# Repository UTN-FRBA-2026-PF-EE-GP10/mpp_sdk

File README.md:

<div align="center">

# mpp-sdk

</div>

A Python SDK for designing, comparing, and deploying **Maximum Power Point
Tracking** (MPPT) algorithms for photovoltaic systems. Built around a clean
hardware-abstraction seam so the same controller code drives a simulation
today and a real SEPIC converter on a Host/sbc tomorrow.

See [`AGENTS.md`](./AGENTS.md) for architectural pillars and contribution
guidelines. Open work is tracked in the
[project tracker issue](https://github.com/UTN-FRBA-2026-PF-EE-GP10/mpp_sdk/issues/128).

## Why

The Python PV ecosystem has a strong **modelling** library
([`pvlib-python`](https://pvlib-python.readthedocs.io/)) but no shared
**control** library. pvlib gives you the panel physics. It does not give
you the closed-loop algorithms that decide where on the I-V curve to
operate. Most MPPT comparison work in the literature uses MATLAB/Simulink,
with code that is rarely released and per-paper bespoke metrics. That
makes cross-paper comparisons and sim-to-real validation hard to
reproduce [Subudhi & Pradhan 2013].

`mpp-sdk` closes that gap with four contributions:

1. **A uniform `MPPTAlgorithm.step(V, I) → D` interface.** A new
   controller is a one-file PR, and the comparison harness treats it like
   every other algorithm.
2. **A hardware-abstraction seam (`SignalSource`).** The same algorithm
   code runs against a `SimulatedSource` or a real power-electronics
   board, with no branches in the algorithm.
3. **A microcontroller as the deployment target.** A small MCU
   (Raspberry Pi Pico / RP2040) drives the power stage, connected to the
   Host/sbc over SPI. This isolates the fast-switching, high-current
   side from the Host/sbc, and gives the project its deployment target: once an
   algorithm is validated in the framework, it is ported to the MCU and
   re-run end to end on the same physical rig.
4. **A reproducible comparison harness.** Dynamic irradiance profiles,
   shared metrics (tracking efficiency, settling time, steady-state
   oscillation, trap depth), and paper figures regenerated from code.

> **The thesis deliverable is an MCU-deployable algorithm that fits a
> Pico-class chip and performs competitively with classical methods.**
> The same codebase both develops it and compares it against the
> established literature. The MCU-deployment requirement is also a useful
> design constraint: it favors fixed-step, minimal-state methods, which
> also happen to be the easiest to analyse.

The design reasoning and the related-work background live in
[`docs/rationale.md`](docs/rationale.md) and
[`docs/general_information.md`](docs/general_information.md).

## Installation

Once published to PyPI, install with `uv` (recommended) or `pip`:

```bash
# Core library - panel models, SEPIC converter, P&O, SimulatedSource
uv add mpp-sdk

# With high-fidelity pvlib panel models (PvlibPanelModel adapter)
uv add "mpp-sdk[pvlib]"

# With SPI hardware dependencies (Phase 5 - SpiMcuSource)
uv add "mpp-sdk[hardware]"

# With the curve-tracer FastAPI web backend (mpp-sdk curve-tracer-web)
uv add "mpp-sdk[web]"

# Everything at once
uv add "mpp-sdk[all]"
```

Then import from your project:

```python
import mpp_sdk

panel = mpp_sdk.IdealSingleDiode()
conv  = mpp_sdk.SEPICConverter()
src   = mpp_sdk.SimulatedSource(panel, conv, load_resistance=10.0)
ctl   = mpp_sdk.PerturbAndObserve(initial_duty=src.duty, min_duty=0.1, max_duty=0.9)

for _ in range(500):
    v, i = src.read()
    src.write(ctl.step(v, i))
```

## Quickstart (development)

Clone the repo and run the live demo directly:

```bash
git clone https://github.com/UTN-FRBA-2026-PF-EE-GP10/mpp_sdk.git
cd mpp_sdk
uv sync
uv run main.py
```

This runs Perturb & Observe MPPT against the ideal single-diode panel model
and plots the I-V / P-V curves with the calculated MPP and the algorithm's
operating-point trajectory.

Every other runnable script under `harness/`, `examples/`, and `scripts/`
is also reachable through one dispatcher, `mpp-sdk`
(`examples/pno_demo.py` is a thin shim to this same `main.py` quickstart,
so it is not a separate entry):

```bash
uv run mpp-sdk --help              # list every runnable script
uv run mpp-sdk compare-dynamic     # run harness/compare_dynamic.py
uv run mpp-sdk animate --shade     # forwards extra flags to the target script
```

Each script also stays directly runnable on its own (e.g.
`uv run harness/compare_dynamic.py`) - `mpp-sdk` is just a single place to
discover them all.

### Curve-tracer web workbench

A React frontend + FastAPI backend for capturing, browsing, and replaying
real panel I-V curves - see [`frontend/README.md`](frontend/README.md) for
the full picture. Try it with no hardware at all:

```bash
uv sync --extra web
uv run mpp-sdk curve-tracer-web --demo
# open http://localhost:8000/
```

Drop `--demo` (and add `--extra hardware`) once a Raspberry Pi + RP2040
board is wired up per
[`firmware/pipico_board/README.md`](firmware/pipico_board/README.md).

### Closed-loop runs

`mpp-sdk run-algorithm --algorithm "P&O" --duration-s 10 --label bench-check`
sweeps a ground-truth I-V curve, then runs a registered algorithm against
the live board for a while, recording `(t, V, I, D)`. Plot it with
`mpp-sdk plot-run`. Needs real hardware (`--extra hardware`).

## Layout

```text
mpp_sdk/
├── models/         # Solar panel I-V models  (PanelModel ABC; ideal, pvlib, string, tabulated, measured)
├── converters/     # Power-stage models      (SEPICConverter)
├── algorithms/     # MPPT controllers        (MPPTAlgorithm ABC; P&O, InCond, fuzzy, scan, PSO)
├── io/             # Hardware-abstraction    (SignalSource ABC; simulated, dynamic, noisy, SPI to the Pico)
├── curves/         # Captured I-V curve library (CurveRecord, feeds MeasuredPanel)
├── runs/           # Captured closed-loop runs (RunRecord)
├── sessions/       # Bench session checklists and their templates
├── panels/         # Panel model library (label values)
├── metrics.py      # Comparison metrics
└── visualization.py

harness/            # Comparison scripts (static, dynamic, live, cyclic ranking, sim-to-real bank)
scripts/            # Bench tools and the workbench server (FastAPI)
frontend/           # Workbench UI (React); its build is committed to scripts/curve_tracer_web/
firmware/           # RP2040 firmware (Rust) and its host-tested safety-checks crate
hardware/           # KiCad board
data/               # Bench data (see data/README.md)
docs/               # Algorithm references, rationale, procedures
```

The control variable is always the SEPIC **duty cycle**. The measured
quantities are always panel terminal **voltage** and **current**. Richer
panel models may depend on temperature, irradiance, or a measured curve,
but those inputs live on the *model* - the controller never sees them.

## Where mpp-sdk sits relative to pvlib

[`pvlib-python`](https://pvlib-python.readthedocs.io/) is the de-facto
open-source reference for photovoltaic system *performance modelling* in
Python: solar position, irradiance decomposition and transposition,
single- and two-diode I-V solvers, the `bishop88` reverse-bias method for
partial-shading analysis, temperature models, and inverter/energy-yield
calculations [Anderson et al. 2023].

**pvlib does not provide closed-loop MPPT controllers, time-stepping
controller simulation, or hardware abstraction.** Its analytical
`bishop88_mpp` and single-diode MPP solvers return *the* maximum power
point given panel parameters. They do not implement Perturb & Observe,
Incremental Conductance, fuzzy logic, or any other tracking algorithm
that discovers the MPP from a stream of (V, I) measurements.

`mpp-sdk` fills that gap. It is **complementary** to pvlib, not a
replacement:

| Concern                                  | pvlib            | mpp-sdk            |
| ---------------------------------------- | ---------------- | ------------------ |
| Solar resource & irradiance models       | yes              | out of scope       |
| Panel I-V physics (single / two-diode)   | yes (canonical)  | minimal in-tree    |
| Partial shading via `bishop88`           | yes              | wraps pvlib        |
| Closed-loop MPPT controllers (P&O, …)    | **no**           | **yes**            |
| SEPIC / power-stage model                | no               | yes                |
| Hardware abstraction (`SignalSource`)    | no               | yes (Pi + Pico)    |
| Algorithm benchmark / comparison harness | no               | yes                |

The `PvlibPanelModel(PanelModel)` adapter (shipped) drops any pvlib-grade
model behind our controller and converter pipeline, unchanged. We do not
re-implement panel physics that pvlib already provides.

## Status

- **Shipped:** panel models (ideal, pvlib, string, measured), five
  algorithms, the comparison harness, the curve tracer, the web
  workbench, and the Pi + Pico firmware.
- **On hardware:** curves are good. Closed-loop runs work for P&O. The
  other algorithms need a slower, settled control loop first.
- **Open:** a valid hardware comparison, the algorithm port to the Pico,
  and the thesis figures.

Open work is tracked in the [project tracker issue](https://github.com/UTN-FRBA-2026-PF-EE-GP10/mpp_sdk/issues/128).

## Context

This SDK supports an **Electronics Engineering thesis** on MPPT algorithm
comparison. One hard rule applies: **each part of the SDK must work and be
verified in isolation** before it is integrated (see
[`AGENTS.md`](./AGENTS.md), "Definition of done").

The MIT license (see [`LICENSE`](./LICENSE)) covers redistribution. It is
not a warranty: whoever wires this code to real hardware is responsible
for electrical safety and for checking the code against their own
measurements.

## On the use of AI

This project uses large language models (Claude, ChatGPT, Copilot) as
part of its day-to-day toolchain. That is a deliberate choice, not
something to apologise for.

The thesis has **no external funding**. The team is three people with
limited weekly hours. Comparable research groups routinely have either
dedicated funding or AI-assisted workflows, or both. Refusing to use AI
would not buy us purity - it would just widen the resource gap between
this work and the groups it is benchmarked against. We use AI for the
same reason we use `pvlib` instead of re-implementing single-diode
physics: the leverage is real, and the alternative is to do less
science.

That choice has explicit guardrails:

- **Disclose.** The thesis names the LLMs used and the tasks they helped
  with.
- **Verify.** A person reads, understands, and tests every LLM-assisted
  change before it merges.
- **Cite.** When an LLM reproduces a known algorithm or formula, the
  change cites the primary reference.
- **Author.** A person is the author of every commit and is accountable
  for it.
- **Off-limits.** Numerical results, measured data, experimental claims,
  and conclusions are written and checked by the human authors.

## References

The bibliography below is the working set the project cites; it will grow
as algorithms and models land.

### Reference Python framework

- **[Anderson et al. 2023]** Anderson, K. S., Hansen, C. W., Holmgren,
  W. F., Jensen, A. R., Mikofski, M. A., & Driesse, A. (2023). *pvlib
  python: 2023 project update.* Journal of Open Source Software,
  **8**(92), 5994. <https://doi.org/10.21105/joss.05994>
- **[Holmgren et al. 2018]** Holmgren, W. F., Hansen, C. W., & Mikofski,
  M. A. (2018). *pvlib python: a python package for modeling solar
  energy systems.* Journal of Open Source Software, **3**(29), 884.
  <https://doi.org/10.21105/joss.00884>

### Panel modelling

- **[De Soto et al. 2006]** De Soto, W., Klein, S. A., & Beckman, W. A.
  (2006). *Improvement and validation of a model for photovoltaic array
  performance.* Solar Energy, **80**(1), 78-88. (Single-diode model
  parameter extraction.)

### MPPT algorithm reviews and canonical methods

- **[Andriniriniaimalaza et al. 2025]** Andriniriniaimalaza, F. P., Murad,
  N. M., Balan, G., Bilal, H., Randriatefison, N., Khoodaruth, A.,
  Andrianirina, C. B., & Ravelo, B. (2025). *Hybrid Fuzzy Logic and
  Shading-Aware Particle Swarm Optimization for Dynamic Photovoltaic
  Shading Faults Mitigation.* arXiv. <https://doi.org/10.48550/arXiv.2512.08419>
- **[Subudhi & Pradhan 2013]** Subudhi, B., & Pradhan, R. (2013). *A
  comparative study on maximum power point tracking techniques for
  photovoltaic power systems.* IEEE Transactions on Sustainable Energy,
  **4**(1), 89-98.
- **[Hussein et al. 1995]** Hussein, K. H., Muta, I., Hoshino, T., &
  Osakada, M. (1995). *Maximum photovoltaic power tracking: an
  algorithm for rapidly changing atmospheric conditions.* IEE
  Proceedings - Generation, Transmission and Distribution, **142**(1),
  59-64. (Incremental Conductance reference implementation.)
- **[Femia et al. 2005]** Femia, N., Petrone, G., Spagnuolo, G., &
  Vitelli, M. (2005). *Optimization of perturb and observe maximum
  power point tracking method.* IEEE Transactions on Power Electronics,
  **20**(4), 963-973. (P&O step-size design.)
- **[Kobayashi et al. 2006]** Kobayashi, K., Takano, I., & Sawada, Y.
  (2006). *A study of a two stage maximum power point tracking control of
  a photovoltaic system under partially shaded insolation conditions.*
  Solar Energy Materials and Solar Cells, **90**(18), 2975-2988.

### Partial shading and Global MPPT

- **[Patel & Agarwal 2008]** Patel, H., & Agarwal, V. (2008). *Maximum
  power point tracking scheme for PV systems operating under partially
  shaded conditions.* IEEE Transactions on Industrial Electronics,
  **55**(4), 1689-1698.
- **[Miyatake et al. 2011]** Miyatake, M., Veerachary, M., Toriumi, F.,
  Fujii, N., & Ko, H. (2011). *Maximum power point tracking of multiple
  photovoltaic arrays: a PSO approach.* IEEE Transactions on Aerospace
  and Electronic Systems, **47**(1), 367-380.
- **[Liu et al. 2012]** Liu, Y.-H., Huang, S.-C., Huang, J.-W., & Liang,
  W.-C. (2012). *A particle swarm optimization-based maximum power
  point tracking algorithm for PV systems operating under partially
  shaded conditions.* IEEE Transactions on Energy Conversion, **27**(4),
  1027-1035.

### Standards and benchmarking

- **[EN 50530]** CENELEC EN 50530:2010+A1:2013. *Overall efficiency of
  grid connected photovoltaic inverters.* (Defines the MPPT
  static- and dynamic-efficiency test profiles used as the comparison
  harness target.)

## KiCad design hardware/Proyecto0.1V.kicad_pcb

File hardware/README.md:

# Hardware

KiCad source for the Proyecto 0.1V board, plus generated fabrication/export
artifacts. Source and generated files live side by side in this folder -
here's which is which.

## Source (edit these)

- `Proyecto0.1V.kicad_pro`, `Proyecto0.1V.kicad_pcb` - the KiCad project and
  PCB layout.
- `Proyecto0.1V.kicad_sch`, `Pico.kicad_sch`, `SepicConverter.kicad_sch`,
  `supplies.kicad_sch` - hierarchical schematic sheets.
- `untitled.kicad_sch` - despite the name, this **is** live source: the
  AnalogConverters sensing sheet. It's badly named, not stray - don't
  delete or rename it (renaming a sheet file requires a KiCad project-level
  edit for zero functional gain).
- `Custom_Library.pretty/` - custom footprint library used by the layout.

## Generated (regenerate, don't hand-edit)

- `Proyecto0.1V-schematic.pdf`, `Proyecto0.1V-pcb.pdf` - schematic/PCB PDF
  exports, generated with kicad-cli 10.0.1:

  ```sh
  kicad-cli sch export pdf Proyecto0.1V.kicad_sch \
      -o Proyecto0.1V-schematic.pdf
  kicad-cli pcb export pdf Proyecto0.1V.kicad_pcb \
      -o Proyecto0.1V-pcb.pdf \
      -l F.Cu,B.Cu,F.SilkS,B.SilkS,F.Fab,B.Fab,Edge.Cuts \
      --cl Edge.Cuts --mode-multipage --include-border-title
  ```

- `jlcpcb/gerber/`, `jlcpcb/production_files/` - JLCPCB fabrication outputs
  (Gerbers, drill files, BOM, CPL) generated from the KiCad project's own
  fabrication-output tooling.

Regenerate the PDFs and JLCPCB outputs after any schematic/layout change -
don't let them drift from the source files.

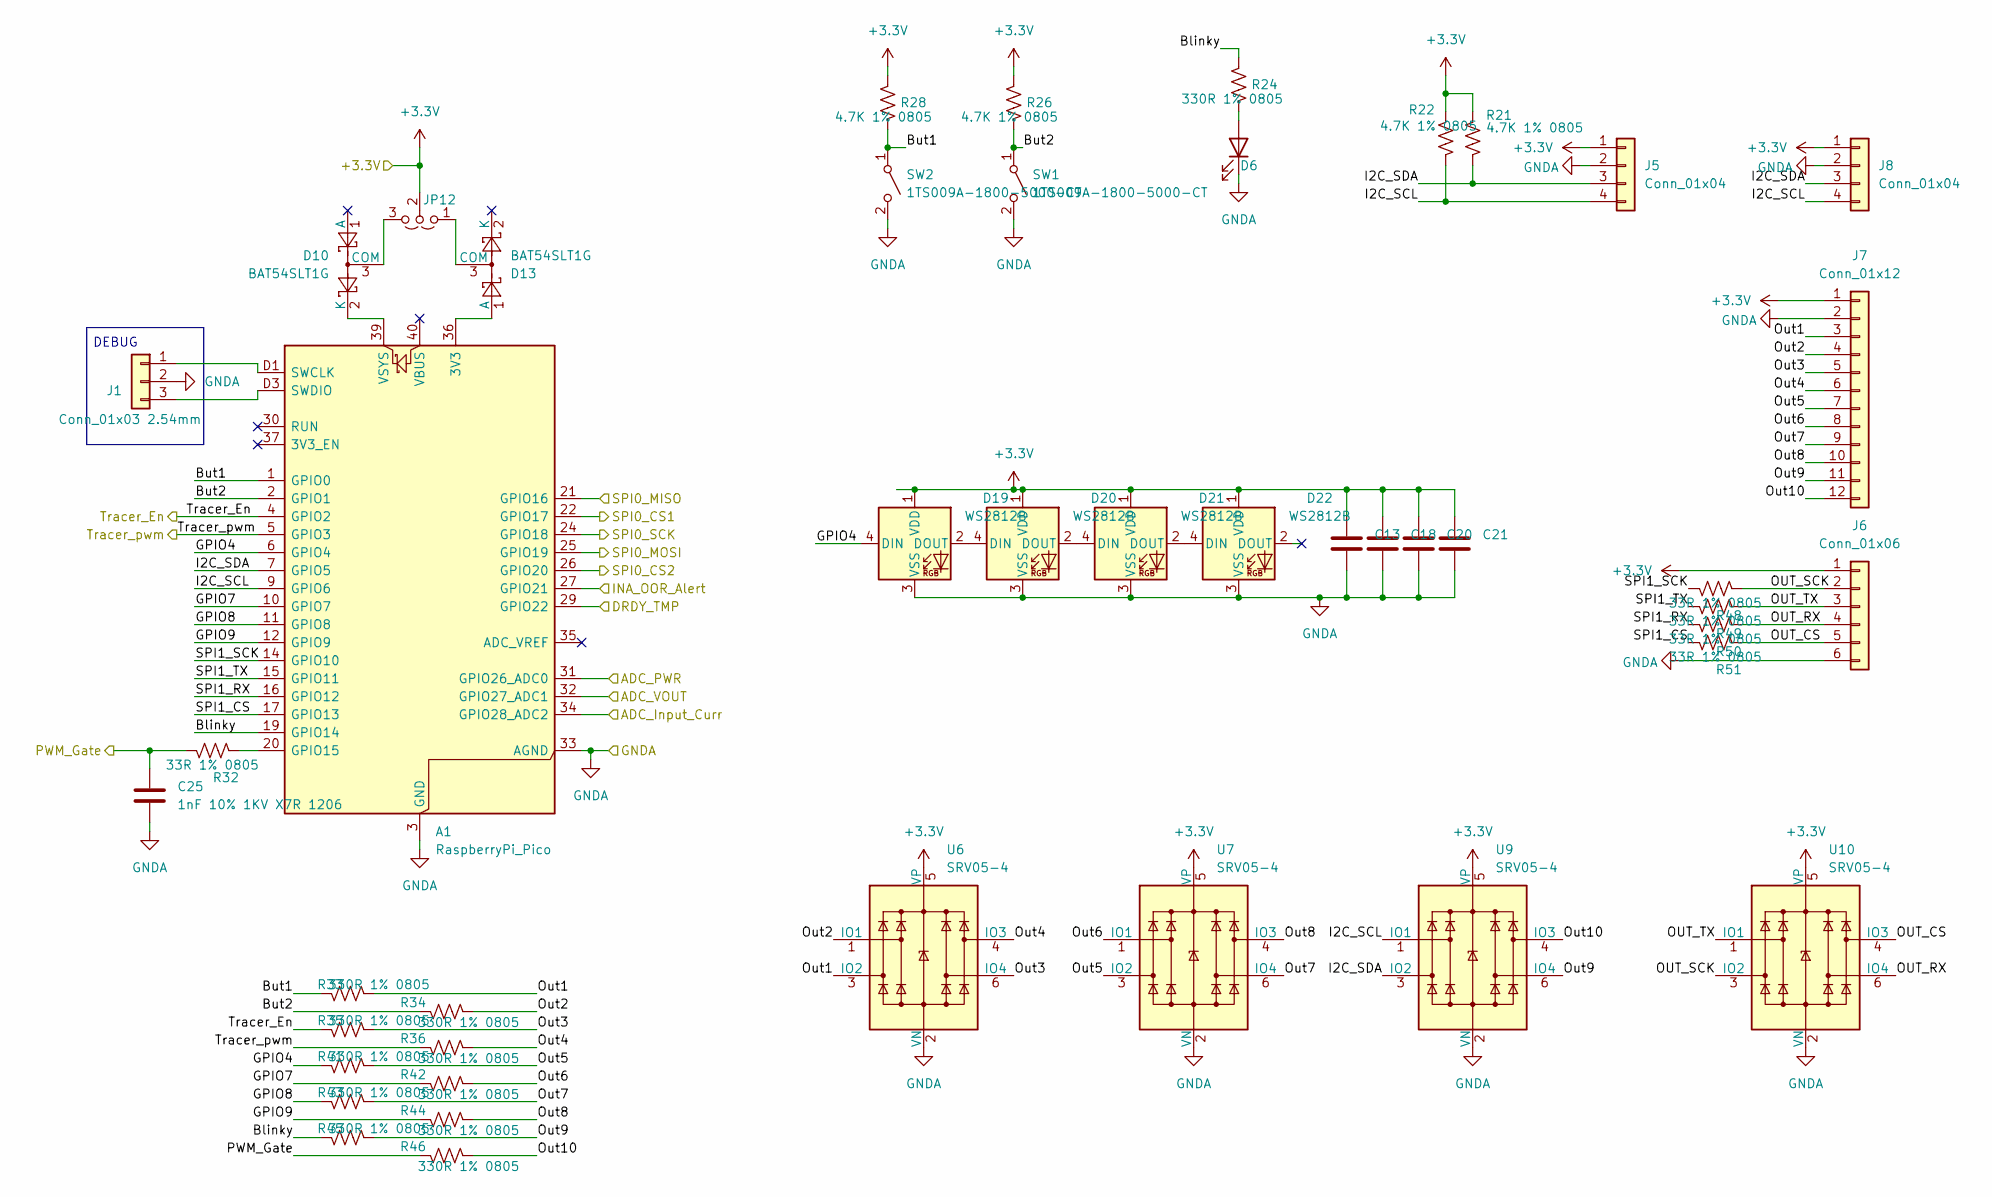
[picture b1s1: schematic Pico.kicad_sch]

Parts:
A1: RaspberryPi_Pico; RaspberryPi_Pico_SMD_HandSolder
C13, C18, C20, C21: 100nF 10% 50V X7R 0805; C_0805_2012Metric
C25: 1nF 10% 1KV X7R 1206; C_1206_3216Metric
D6: YLED0805 Red; LED_0805_2012Metric
D10, D13: BAT54SLT1G; SOT-23; LCSC Part C19726
D19, D20, D21, D22: WS2812B; LED_WS2812B_PLCC4_5.0x5.0mm_P3.2mm
J1: Conn_01x03 2.54mm; PinHeader_1x03_P2.54mm_Vertical
J5, J8: Conn_01x04; PinHeader_1x04_P2.54mm_Vertical
J6: Conn_01x06; PinHeader_1x06_P2.54mm_Vertical
J7: Conn_01x12; PinHeader_1x12_P2.54mm_Vertical
JP12: 2/3 Wire Selector; PinHeader_1x03_P2.54mm_Vertical
R21, R22, R26, R28: 4.7K 1% 0805; R_0805_2012Metric
R24, R33, R34, R35, R36, R41, R42, R43, R44, R45, R46: 330R 1% 0805; R_0805_2012Metric
R32, R48, R49, R50, R51: 33R 1% 0805; R_0805_2012Metric
SW1, SW2: 1TS009A-1800-5000-CT; SW_Push_1TS009xxxx-xxxx-xxxx_6x6x5mm; LCSC Part C319409
U6, U7, U9, U10: SRV05-4; SOT-23-6; LCSC Part C1975211

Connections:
+3.3V: C13.1, C18.1, C20.1, C21.1, D19.1 (VDD), D20.1 (VDD), D21.1 (VDD), D22.1 (VDD), J5.1, J6.1, J7.1, J8.1, JP12.2 (C), R21.2, R22.2, R26.1, R28.1, U6.5 (VP), U7.5 (VP), U9.5 (VP), U10.5 (VP); also elsewhere on the board
/AnalogConverters/ADC_Input_Curr: A1.34 (GPIO28_ADC2); also elsewhere on the board
/AnalogConverters/ADC_VOUT: A1.32 (GPIO27_ADC1); also elsewhere on the board
/AnalogConverters/ADC_VPWR: A1.31 (GPIO26_ADC0); also elsewhere on the board
/AnalogConverters/CS_INA: A1.22 (GPIO17); also elsewhere on the board
/AnalogConverters/CS_TP100: A1.26 (GPIO20); also elsewhere on the board
/AnalogConverters/DRDY_PT100: A1.29 (GPIO22); also elsewhere on the board
/AnalogConverters/INA_OOR_Alert: A1.27 (GPIO21); also elsewhere on the board
/AnalogConverters/SPI_MISO: A1.21 (GPIO16); also elsewhere on the board
/AnalogConverters/SPI_MOSI: A1.25 (GPIO19); also elsewhere on the board
/AnalogConverters/SPI_SCK: A1.24 (GPIO18); also elsewhere on the board
/Pico/Blinky: A1.19 (GPIO14), R24.1, R45.1
/Pico/But1: A1.1 (GPIO0), R28.2, R33.1, SW2.1 (A)
/Pico/But2: A1.2 (GPIO1), R26.2, R34.1, SW1.1 (A)
/Pico/GPIO4: A1.6 (GPIO4), D19.4 (DIN), R41.1
/Pico/GPIO7: A1.10 (GPIO7), R42.1
/Pico/GPIO8: A1.11 (GPIO8), R43.1
/Pico/GPIO9: A1.12 (GPIO9), R44.1
/Pico/I2C_SCL: A1.9 (GPIO6), J5.4, J8.4, R22.1, U9.1 (IO1)
/Pico/I2C_SDA: A1.7 (GPIO5), J5.3, J8.3, R21.1, U9.3 (IO2)
/Pico/OUT_CS: J6.5, R51.2, U10.4 (IO3)
/Pico/OUT_RX: J6.4, R50.2, U10.6 (IO4)
/Pico/OUT_SCK: J6.2, R48.2, U10.3 (IO2)
/Pico/OUT_TX: J6.3, R49.2, U10.1 (IO1)
/Pico/Out1: J7.3, R33.2, U6.3 (IO2)
/Pico/Out2: J7.4, R34.2, U6.1 (IO1)
/Pico/Out3: J7.5, R35.2, U6.6 (IO4)
/Pico/Out4: J7.6, R36.2, U6.4 (IO3)
/Pico/Out5: J7.7, R41.2, U7.3 (IO2)
/Pico/Out6: J7.8, R42.2, U7.1 (IO1)
/Pico/Out7: J7.9, R43.2, U7.6 (IO4)
/Pico/Out8: J7.10, R44.2, U7.4 (IO3)
/Pico/Out9: J7.11, R45.2, U9.6 (IO4)
/Pico/Out10: J7.12, R46.2, U9.4 (IO3)
/Pico/PWM_Gate: C25.1, R32.1, R46.1; also elsewhere on the board
/Pico/SPI1_CS: A1.17 (GPIO13), R51.1
/Pico/SPI1_RX: A1.16 (GPIO12), R50.1
/Pico/SPI1_SCK: A1.14 (GPIO10), R48.1
/Pico/SPI1_TX: A1.15 (GPIO11), R49.1
/Pico/Tracer_En: A1.4 (GPIO2), R35.1; also elsewhere on the board
/Pico/Tracer_pwm: A1.5 (GPIO3), R36.1; also elsewhere on the board
GNDA: A1.3 (GND), A1.8 (GND), A1.13 (GND), A1.18 (GND), A1.23 (GND), A1.28 (GND), A1.33 (AGND), A1.38 (GND), A1.D2 (GND), C13.2, C18.2, C20.2, C21.2, C25.2, D6.1 (K), D19.3 (VSS), D20.3 (VSS), D21.3 (VSS), D22.3 (VSS), J1.2, J5.2, J6.6, J7.2, J8.2, SW1.2 (B), SW2.2 (B), U6.2 (VN), U7.2 (VN), U9.2 (VN), U10.2 (VN); also elsewhere on the board
unnamed: A1.36 (3V3), D13.1 (A)
unnamed: A1.20 (GPIO15), R32.2
unnamed: A1.D1 (SWCLK), J1.1
unnamed: A1.D3 (SWDIO), J1.3
unnamed: A1.39 (VSYS), D10.2 (K)
unnamed: D6.2 (A), R24.2
unnamed: D10.3 (COM), JP12.3 (B)
unnamed: D13.3 (COM), JP12.1 (A)
unnamed: D19.2 (DOUT), D20.4 (DIN)
unnamed: D20.2 (DOUT), D21.4 (DIN)
unnamed: D21.2 (DOUT), D22.4 (DIN)

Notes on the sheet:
DEBUG

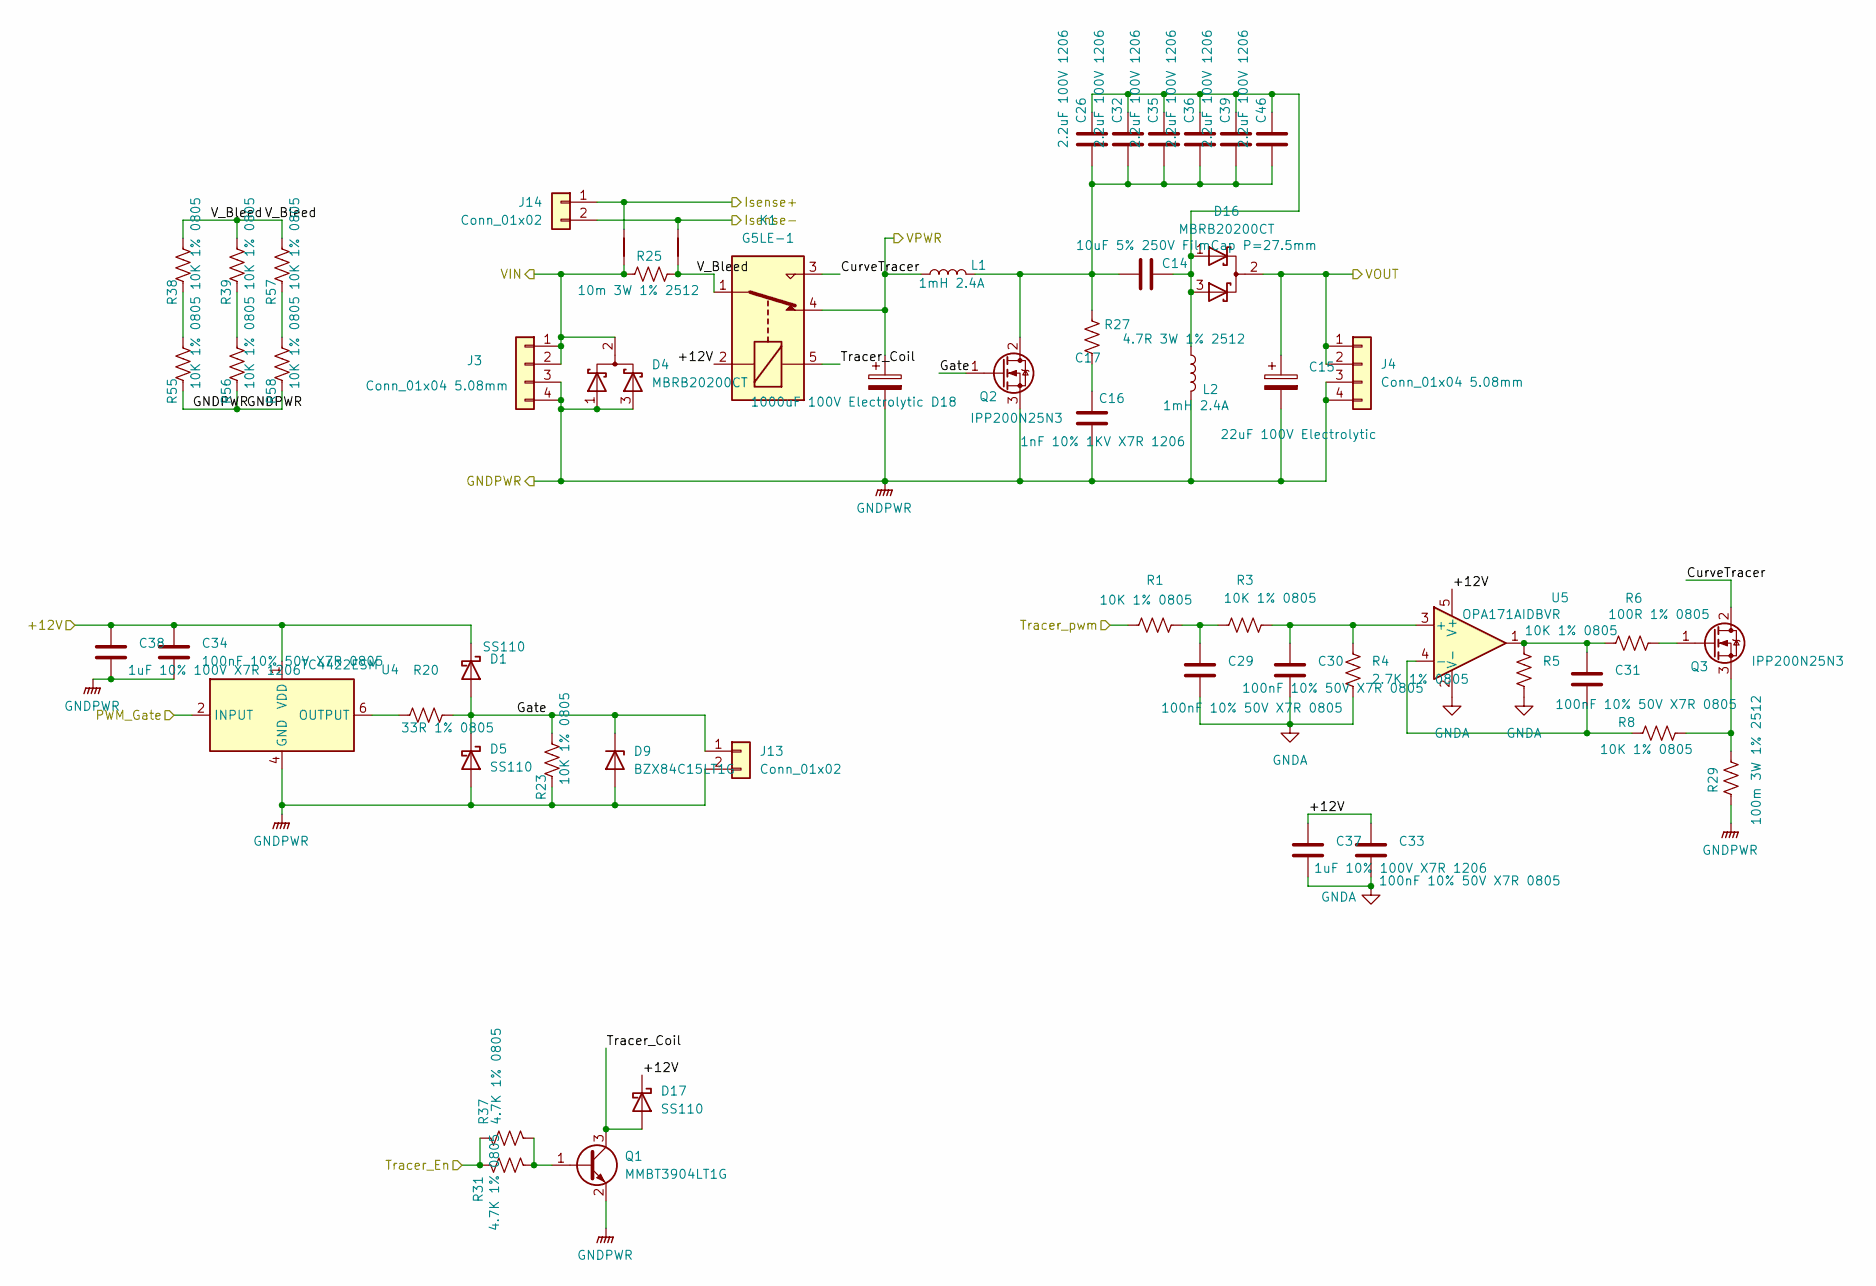
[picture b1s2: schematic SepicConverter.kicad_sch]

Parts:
C14: 10uF 5% 250V FilmCap P=27.5mm; C_Rect_L31.5mm_W17.0mm_P27.50mm_MKS4
C15: 22uF 100V Electrolytic; CP_Radial_D6.3mm_P2.50mm
C16: 1nF 10% 1KV X7R 1206; C_1206_3216Metric
C17: 1000uF 100V Electrolytic D18; CP_Radial_D18.0mm_P7.50mm
C26, C32, C35, C36, C39, C46: 2.2uF 100V 1206; C_1206_3216Metric
C29, C30, C31, C33, C34: 100nF 10% 50V X7R 0805; C_0805_2012Metric
C37, C38: 1uF 10% 100V X7R 1206; C_1206_3216Metric
D1, D5, D17: SS110; D_SMA_Handsoldering
D4, D16: MBRB20200CT; TO-263-2; LCSC Part C3874012
D9: BZX84C15LT1G; SOT-23; LCSC Part C80857
J3, J4: Conn_01x04 5.08mm; TerminalBlock_Phoenix_MKDS-1,5-4-5.08_1x04_P5.08mm_Horizont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
J13, J14: Conn_01x02; PinHeader_1x02_P2.54mm_Vertical
K1: G5LE-1; Relay_SPDT_Omron-G5LE-1
L1, L2: 1mH 2.4A; L_Toroid_Vertical_L31.8mm_W15.9mm_P13.50mm_Bourns_5700
NT1, NT2: NetTie_2; NetTie-2_SMD_Pad0.5mm
Q1: MMBT3904LT1G; SOT-23; LCSC Part C81464
Q2, Q3: IPP200N25N3; TO-220-3_Vertical
R1, R3, R5, R8, R23, R38, R39, R55, R56, R57, R58: 10K 1% 0805; R_0805_2012Metric
R4: 2.7K 1% 0805; R_0805_2012Metric
R6: 100R 1% 0805; R_0805_2012Metric
R20: 33R 1% 0805; R_0805_2012Metric
R25: 10m 3W 1% 2512; R_2512_6332Metric
R27: 4.7R 3W 1% 2512; R_2512_6332Metric
R29: 100m 3W 1% 2512; R_2512_6332Metric
R31, R37: 4.7K 1% 0805; R_0805_2012Metric
U4: TC4422ESM; SOIC-8_5.3x5.3mm_P1.27mm; LCSC Part C638566
U5: OPA171AIDBVR; SOT-23-5; LCSC Part C88036

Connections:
+12V: C33.1, C34.1, C37.1, C38.1, D1.1 (K), D17.1 (K), K1.2, U4.1 (VDD), U4.8 (VDD), U5.5 (V+); also elsewhere on the board
/AnalogConverters/Isense+: J14.1, NT1.2; also elsewhere on the board
/AnalogConverters/Isense-: J14.2, NT2.2; also elsewhere on the board
/AnalogConverters/VIN: D4.2 (K), J3.1, J3.2, NT1.1, R25.1; also elsewhere on the board
/AnalogConverters/VOUT: C15.1, D16.2 (K), J4.1, J4.2; also elsewhere on the board
/AnalogConverters/VPWR: C17.1, K1.4, L1.1; also elsewhere on the board
/Pico/PWM_Gate: U4.2 (INPUT); also elsewhere on the board
/Pico/Tracer_En: R31.2, R37.2; also elsewhere on the board
/Pico/Tracer_pwm: R1.1; also elsewhere on the board
/SepicConverter/CurveTracer: K1.3, Q3.2 (D)
/SepicConverter/Gate: D1.2 (A), D5.1 (K), D9.3 (K), J13.1, Q2.1 (G), R20.2, R23.2
/SepicConverter/Tracer_Coil: D17.2 (A), K1.5, Q1.3 (C)
/SepicConverter/V_Bleed: K1.1, NT2.1, R25.2, R38.2, R39.2, R57.2
GNDA: C29.2, C30.2, C33.2, C37.2, R4.1, R5.1, U5.2 (V-); also elsewhere on the board
GNDPWR: C15.2, C16.1, C17.2, C34.2, C38.2, D4.1 (A), D4.3 (A), D5.2 (A), D9.1 (A), J3.3, J3.4, J4.3, J4.4, J13.2, L2.2, Q1.2 (E), Q2.3 (S), R23.1, R29.1, R55.1, R56.1, R58.1, U4.4 (GND), U4.5 (GND); also elsewhere on the board
unnamed: C14.2, C26.2, C32.2, C35.2, C36.2, C39.2, C46.2, D16.1 (A), D16.3 (A), L2.1
unnamed: C16.2, R27.1
unnamed: C29.1, R1.2, R3.1
unnamed: C31.1, R5.2, R6.2, U5.1
unnamed: Q1.1 (B), R31.1, R37.1
unnamed: C14.1, C26.1, C32.1, C35.1, C36.1, C39.1, C46.1, L1.2, Q2.2 (D), R27.2
unnamed: Q3.1 (G), R6.1
unnamed: Q3.3 (S), R8.1, R29.2
unnamed: R20.1, U4.6 (OUTPUT), U4.7 (OUTPUT)
unnamed: R38.1, R55.2
unnamed: R39.1, R56.2
unnamed: R57.1, R58.2
unnamed: C30.1, R3.2, R4.2, U5.3 (+)
unnamed: C31.2, R8.2, U5.4 (-)

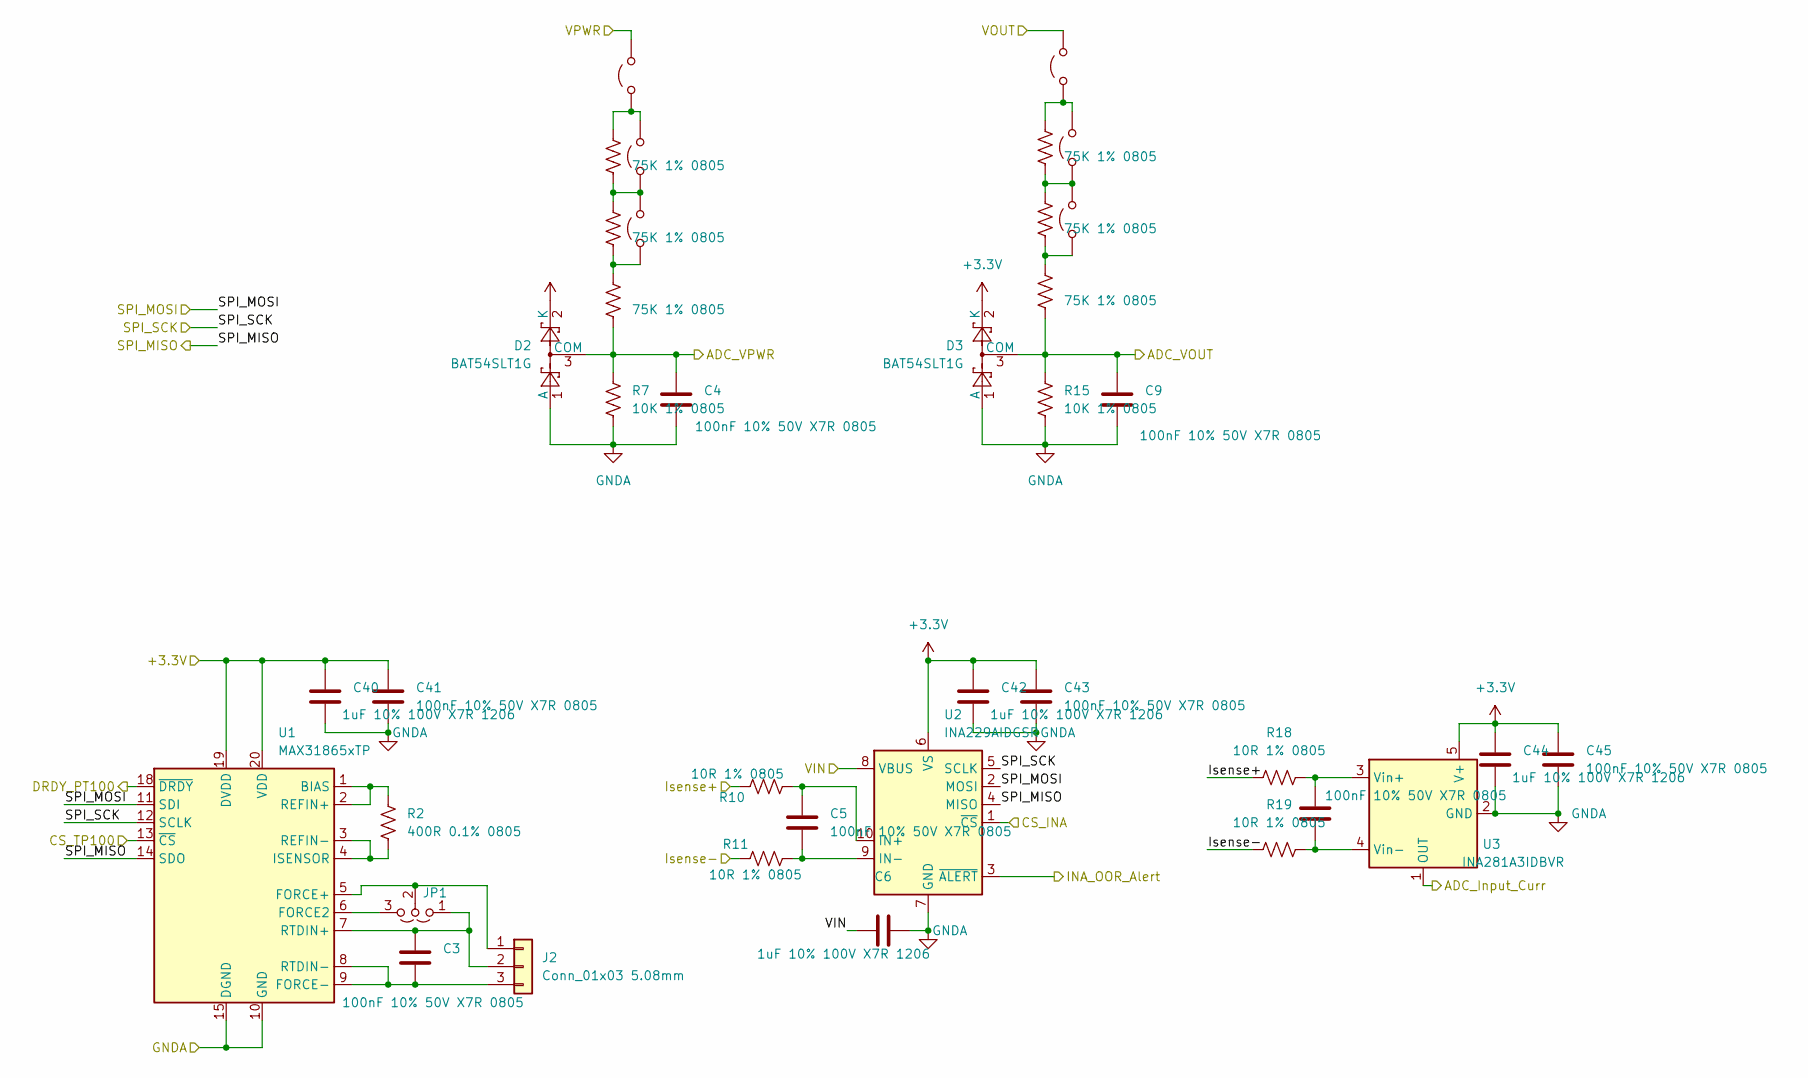
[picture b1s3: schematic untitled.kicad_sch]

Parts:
C3, C4, C5, C9, C10, C41, C43, C45: 100nF 10% 50V X7R 0805; C_0805_2012Metric
C6, C40, C42, C44: 1uF 10% 100V X7R 1206; C_1206_3216Metric
D2, D3: BAT54SLT1G; SOT-23; LCSC Part C19726
J2: Conn_01x03 5.08mm; TerminalBlock_Phoenix_MKDS-1,5-3-5.08_1x03_P5.08mm_Horizont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
JP1: 2/3 Wire Selector; PinHeader_1x03_P2.54mm_Vertical
JP6, JP7, JP8, JP9, JP10, JP13: Jumper_2_Open; PinHeader_1x02_P2.54mm_Vertical
R2: 400R 0.1% 0805; R_0805_2012Metric
R7, R15: 10K 1% 0805; R_0805_2012Metric
R10, R11, R18, R19: 10R 1% 0805; R_0805_2012Metric
R12, R13, R14, R16, R17, R30: 75K 1% 0805; R_0805_2012Metric
U1: MAX31865xTP; TQFN-20-1EP_5x5mm_P0.65mm_EP3.25x3.25mm; LCSC Part C118474
U2: INA229AIDGSR; TSSOP-10_3x3mm_P0.5mm; LCSC Part C2846803
U3: INA281A3IDBVR; SOT-23-5; LCSC Part C1517407

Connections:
+3.3V: C40.1, C41.1, C42.1, C43.1, C44.1, C45.1, D2.2 (K), D3.2 (K), U1.19 (DVDD), U1.20 (VDD), U2.6 (VS), U3.5 (V+); also elsewhere on the board
/AnalogConverters/ADC_Input_Curr: U3.1 (OUT); also elsewhere on the board
/AnalogConverters/ADC_VOUT: C9.1, D3.3 (COM), R15.1, R30.2; also elsewhere on the board
/AnalogConverters/ADC_VPWR: C4.1, D2.3 (COM), R7.1, R14.2; also elsewhere on the board
/AnalogConverters/CS_INA: U2.1 (~CS); also elsewhere on the board
/AnalogConverters/CS_TP100: U1.13 (~CS); also elsewhere on the board
/AnalogConverters/DRDY_PT100: U1.18 (~DRDY); also elsewhere on the board
/AnalogConverters/INA_OOR_Alert: U2.3 (~ALERT); also elsewhere on the board
/AnalogConverters/Isense+: R10.1, R18.1; also elsewhere on the board
/AnalogConverters/Isense-: R11.1, R19.1; also elsewhere on the board
/AnalogConverters/SPI_MISO: U1.14 (SDO), U2.4 (MISO); also elsewhere on the board
/AnalogConverters/SPI_MOSI: U1.11 (SDI), U2.2 (MOSI); also elsewhere on the board
/AnalogConverters/SPI_SCK: U1.12 (SCLK), U2.5 (SCLK); also elsewhere on the board
/AnalogConverters/VIN: C6.1, U2.8 (VBUS); also elsewhere on the board
/AnalogConverters/VOUT: JP10.2 (B); also elsewhere on the board
/AnalogConverters/VPWR: JP9.2 (B); also elsewhere on the board
GNDA: C4.2, C6.2, C9.2, C40.2, C41.2, C42.2, C43.2, C44.2, C45.2, D2.1 (A), D3.1 (A), R7.2, R15.2, U1.10 (GND), U1.15 (DGND), U1.16 (GND), U1.21 (GND), U2.7 (GND), U3.2 (GND); also elsewhere on the board
unnamed: J2.1, JP1.2 (C), U1.5 (FORCE+)
unnamed: C3.1, J2.2, JP1.1 (A), U1.7 (RTDIN+)
unnamed: C3.2, J2.3, U1.8 (RTDIN-), U1.9 (FORCE-)
unnamed: JP1.3 (B), U1.6 (FORCE2)
unnamed: JP6.1 (A), JP7.2 (B), R12.1, R13.2
unnamed: JP6.2 (B), JP9.1 (A), R13.1
unnamed: JP7.1 (A), R12.2, R14.1
unnamed: JP8.2 (B), JP10.1 (A), R16.1
unnamed: JP13.1 (A), R17.2, R30.1
unnamed: JP8.1 (A), JP13.2 (B), R16.2, R17.1
unnamed: R2.2, U1.1 (BIAS), U1.2 (REFIN+)
unnamed: R2.1, U1.3 (REFIN-), U1.4 (ISENSOR)
unnamed: C5.1, R10.2, U2.10 (IN+)
unnamed: C5.2, R11.2, U2.9 (IN-)
unnamed: C10.1, R18.2, U3.3 (Vin+)
unnamed: C10.2, R19.2, U3.4 (Vin-)

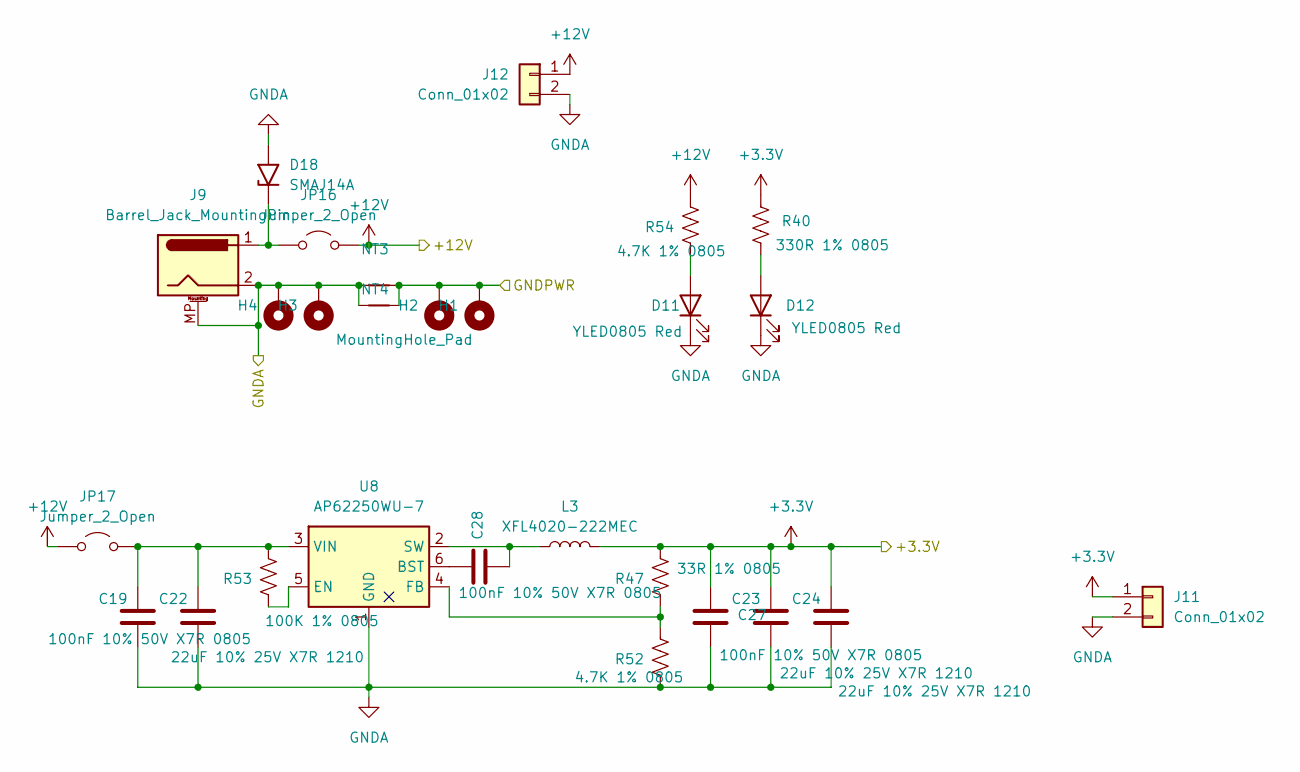
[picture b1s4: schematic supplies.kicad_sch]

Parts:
C19, C27, C28: 100nF 10% 50V X7R 0805; C_0805_2012Metric
C22, C23, C24: 22uF 10% 25V X7R 1210; C_1210_3225Metric
D11, D12: YLED0805 Red; LED_0805_2012Metric
D18: SMAJ14A; D_SMA; LCSC Part C99286
H1, H2, H3, H4: MountingHole_Pad; MountingHole_3.2mm_M3_Pad
J9: Barrel_Jack_MountingPin; BarrelJack_GCT_DCJ200-10-A_Horizontal
J11, J12: Conn_01x02; PinHeader_1x02_P2.54mm_Vertical
JP16, JP17: Jumper_2_Open; PinHeader_1x02_P2.54mm_Vertical
L3: XFL4020-222MEC; L_Wurth_WE-LQSH-4020; LCSC Part C122469
NT3, NT4: NetTie_2; NetTie-2_SMD_Pad2.0mm
R40: 330R 1% 0805; R_0805_2012Metric
R47: 33R 1% 0805; R_0805_2012Metric
R52, R54: 4.7K 1% 0805; R_0805_2012Metric
R53: 100K 1% 0805; R_0805_2012Metric
U8: AP62250WU-7; TSOT-23-6; LCSC Part C5184228

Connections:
+3.3V: C23.1, C24.1, C27.1, J11.1, L3.2, R40.1, R47.1; also elsewhere on the board
+12V: J12.1, JP16.1 (A), JP17.1 (A), R54.1; also elsewhere on the board
GNDA: C19.2, C22.2, C23.2, C24.2, C27.2, D11.1 (K), D12.1 (K), D18.2 (A2), H3.1 (1_1), H4.1 (1_1), J9.2, J9.3, J9.MP (MountPin), J11.2, J12.2, NT3.1, NT4.1, R52.2, U8.1 (GND); also elsewhere on the board
GNDPWR: H1.1 (1_1), H2.1 (1_1), NT3.2, NT4.2; also elsewhere on the board
unnamed: D11.2 (A), R54.2
unnamed: D12.2 (A), R40.2
unnamed: D18.1 (A1), J9.1, JP16.2 (B)
unnamed: C19.1, C22.1, JP17.2 (B), R53.1, U8.3 (VIN)
unnamed: C28.1, U8.6 (BST)
unnamed: R53.2, U8.5 (EN)
unnamed: R47.2, R52.1, U8.4 (FB)
unnamed: C28.2, L3.1, U8.2 (SW)
